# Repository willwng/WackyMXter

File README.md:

# WackyMXter
my custom keyboard.

## Features
- Wireless (bluetooth)
- Split (two halves can also be independent)
- Supports Choc and MX hotswap switches
- Ergonomic (for my hands at least)
- ZMK Support

## Project Format
- `gerber/`: Gerber files for the left and right side (includes BOM and placement files for assembly of shift register and diodes)
- `layout-editor/`: Layout of the keyboard for use at [keyboard layout editor](http://www.keyboard-layout-editor.com/)
- `pcb/`: KiCad files
- `zmk-firmware/`: Links to the ZMK firmware repo: [WackyMXter-zmk-firmware](https://github.com/willwng/WackyMXter-zmk-config)

## Materials
| **Item**              | **Quantity Required (per set)** |
|-----------------------|---------------------------------|
| PCBs                  |                               2 |
| [Xiao BLE](https://www.seeedstudio.com/Seeed-XIAO-BLE-nRF52840-p-5201.html)              |                               2 |
| Rotary Encoder        |                               2 |
| Encoder Knob          |                               2 |
| Hotswap Sockets       |                              68 |
| Choc Switches         |                              68 |
| Power Switch          |                               2 |
| JST Battery Connector |                               2 |
| LiPo Battery          |                               2 |
| Keycaps               |                              68 |

The power switch, JST connector, and LiPo battery are optional if you want the board to be wired (but this requires powering both halves)

## Notes
- Unless you update the footprint, be sure to get EC11(E) rotary encoder <- "E" being the key. I got an EC11(R) encoder and the legs didn't fit, causing me to clip them.
- I messed up the placement of the JST connector - it stands higher than the hotswap sockets, so for a caseless build it is unfortunately too tall to be on the bottom. I ended up mounting it on the front, but backward (to not interfere with the power switch), so this required reversing the polarity of the batteries

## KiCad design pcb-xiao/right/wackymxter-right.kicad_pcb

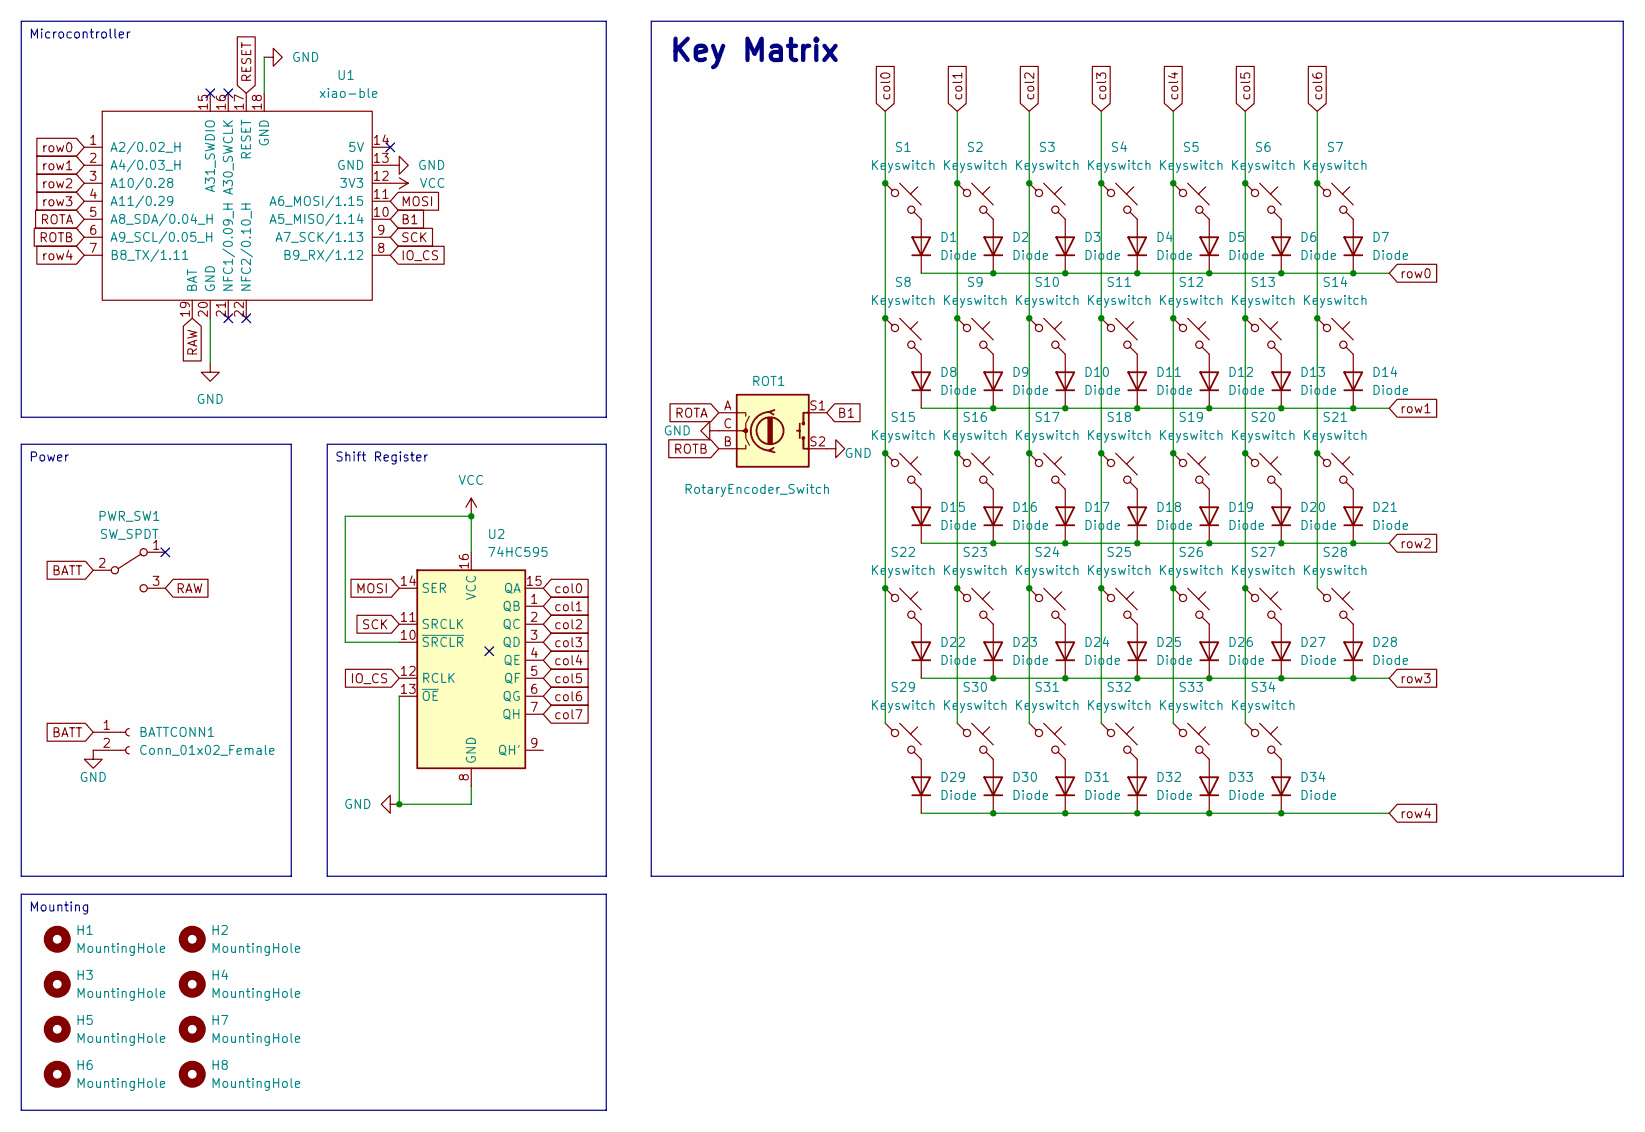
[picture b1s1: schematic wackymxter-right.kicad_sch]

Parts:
BATTCONN1: Conn_01x02_Female; JST_PH_S2B-PH-K_1x02_P2.00mm_Horizontal
D1, D2, D3, D4, D5, D6, D7, D8, D9, D10, D11, D12, D13, D14, D15, D16, D17, D18, D19, D20, D21, D22, D23, D24, D25, D26, D27, D28, D29, D30, D31, D32, D33, D34: Diode; HybridDiode
H1, H2, H3, H4, H5, H6, H7, H8: MountingHole; MountingHole_2.2mm_M2
PWR_SW1: SW_SPDT; SW_SPDT_CK_JS102011SAQN
ROT1: RotaryEncoder_Switch; RotaryEncoder_Alps_EC11E-Switch_Vertical_H20mm
S1, S2, S3, S4, S5, S6, S7, S8, S9, S10, S11, S12, S13, S14, S15, S16, S17, S18, S19, S20, S21, S22, S23, S24, S25, S26, S27, S28, S29, S30, S31, S32, S33, S34: Keyswitch; MX_Choc_Hotswap
U1: xiao-ble; xiao-ble-smd-cutout
U2: 74HC595; SOP-16_3.9x9.9mm_P1.27mm

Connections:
B1: ROT1.S1, U1.10 (A5_MISO/1.14)
BATT: BATTCONN1.1, PWR_SW1.2 (B)
GND: BATTCONN1.2, ROT1.C, ROT1.S2, U1.13 (GND), U1.18 (GND), U1.20 (GND), U2.8 (GND), U2.13 (~OE)
IO_CS: U1.8 (B9_RX/1.12), U2.12 (RCLK)
MOSI: U1.11 (A6_MOSI/1.15), U2.14 (SER)
unnamed: D1.2 (A), S1.2
unnamed: D2.2 (A), S2.2
unnamed: D3.2 (A), S3.2
unnamed: D4.2 (A), S4.2
unnamed: D5.2 (A), S5.2
unnamed: D6.2 (A), S6.2
unnamed: D7.2 (A), S7.2
unnamed: D8.2 (A), S8.2
unnamed: D9.2 (A), S9.2
unnamed: D10.2 (A), S10.2
unnamed: D11.2 (A), S11.2
unnamed: D12.2 (A), S12.2
unnamed: D13.2 (A), S13.2
unnamed: D14.2 (A), S14.2
unnamed: D15.2 (A), S15.2
unnamed: D16.2 (A), S16.2
unnamed: D17.2 (A), S17.2
unnamed: D18.2 (A), S18.2
unnamed: D19.2 (A), S19.2
unnamed: D20.2 (A), S20.2
unnamed: D21.2 (A), S21.2
unnamed: D22.2 (A), S22.2
unnamed: D23.2 (A), S23.2
unnamed: D24.2 (A), S24.2
unnamed: D25.2 (A), S25.2
unnamed: D26.2 (A), S26.2
unnamed: D27.2 (A), S27.2
unnamed: D28.2 (A), S28.2
unnamed: D29.2 (A), S29.2
unnamed: D30.2 (A), S30.2
unnamed: D31.2 (A), S31.2
unnamed: D32.2 (A), S32.2
unnamed: D33.2 (A), S33.2
unnamed: D34.2 (A), S34.2
RAW: PWR_SW1.3 (C), U1.19 (BAT)
RESET: U1.17 (RESET)
ROTA: ROT1.A, U1.5 (A8_SDA/0.04_H)
ROTB: ROT1.B, U1.6 (A9_SCL/0.05_H)
SCK: U1.9 (A7_SCK/1.13), U2.11 (SRCLK)
VCC: U1.12 (3V3), U2.10 (~SRCLR), U2.16 (VCC)
col0: S1.1, S8.1, S15.1, S22.1, S29.1, U2.15 (QA)
col1: S2.1, S9.1, S16.1, S23.1, S30.1, U2.1 (QB)
col2: S3.1, S10.1, S17.1, S24.1, S31.1, U2.2 (QC)
col3: S4.1, S11.1, S18.1, S25.1, S32.1, U2.3 (QD)
col4: S5.1, S12.1, S19.1, S26.1, S33.1, U2.4 (QE)
col5: S6.1, S13.1, S20.1, S27.1, S34.1, U2.5 (QF)
col6: S7.1, S14.1, S21.1, S28.1, U2.6 (QG)
col7: U2.7 (QH)
row0: D1.1 (K), D2.1 (K), D3.1 (K), D4.1 (K), D5.1 (K), D6.1 (K), D7.1 (K), U1.1 (A2/0.02_H)
row1: D8.1 (K), D9.1 (K), D10.1 (K), D11.1 (K), D12.1 (K), D13.1 (K), D14.1 (K), U1.2 (A4/0.03_H)
row2: D15.1 (K), D16.1 (K), D17.1 (K), D18.1 (K), D19.1 (K), D20.1 (K), D21.1 (K), U1.3 (A10/0.28)
row3: D22.1 (K), D23.1 (K), D24.1 (K), D25.1 (K), D26.1 (K), D27.1 (K), D28.1 (K), U1.4 (A11/0.29)
row4: D29.1 (K), D30.1 (K), D31.1 (K), D32.1 (K), D33.1 (K), D34.1 (K), U1.7 (B8_TX/1.11)

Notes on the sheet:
Microcontroller
Power
Shift Register
Key Matrix
Mounting

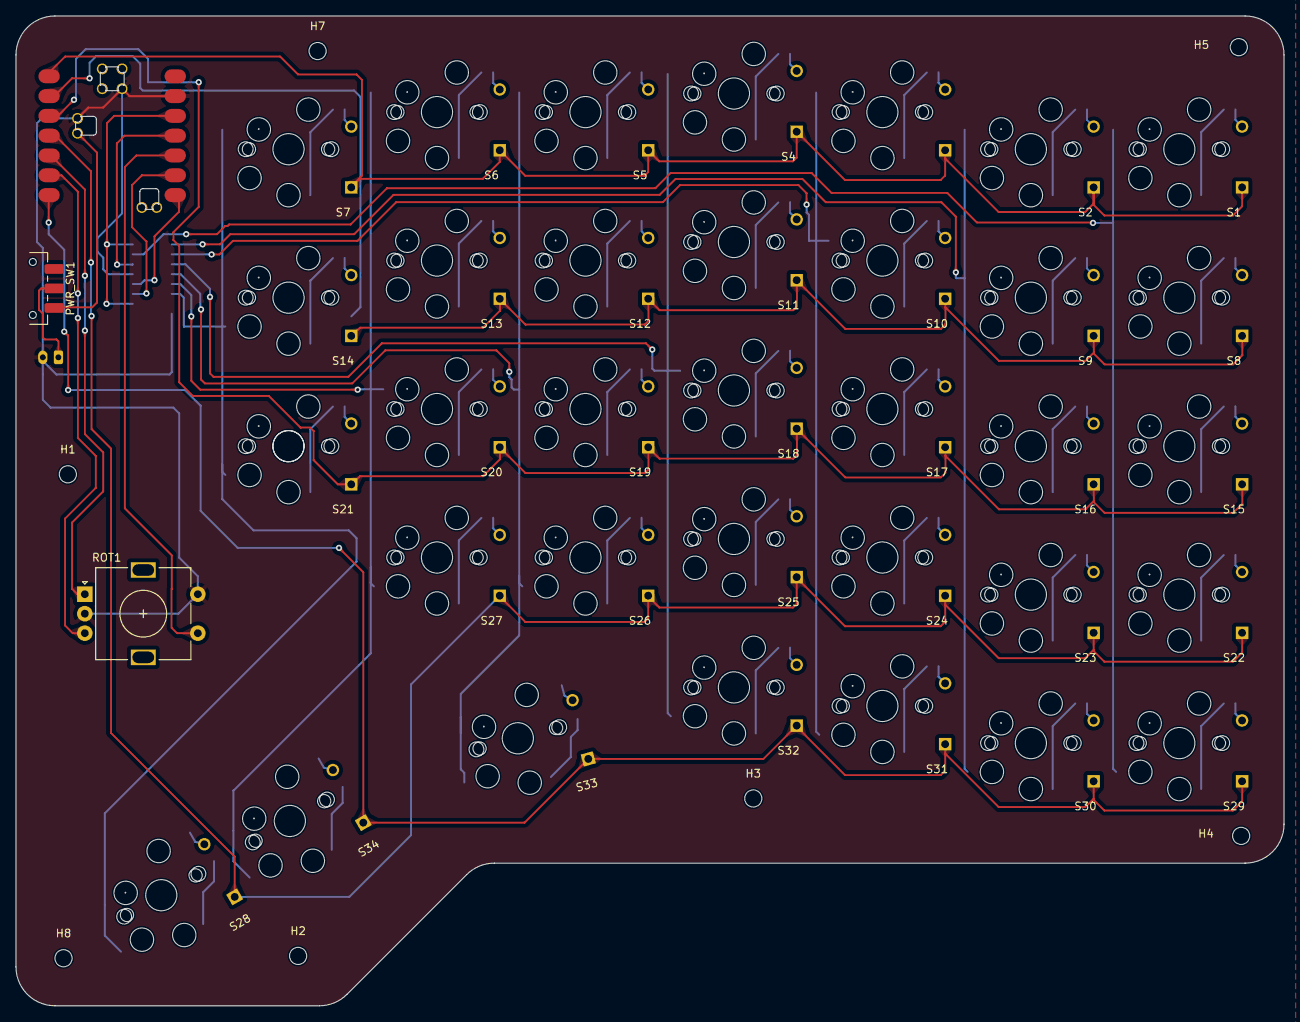
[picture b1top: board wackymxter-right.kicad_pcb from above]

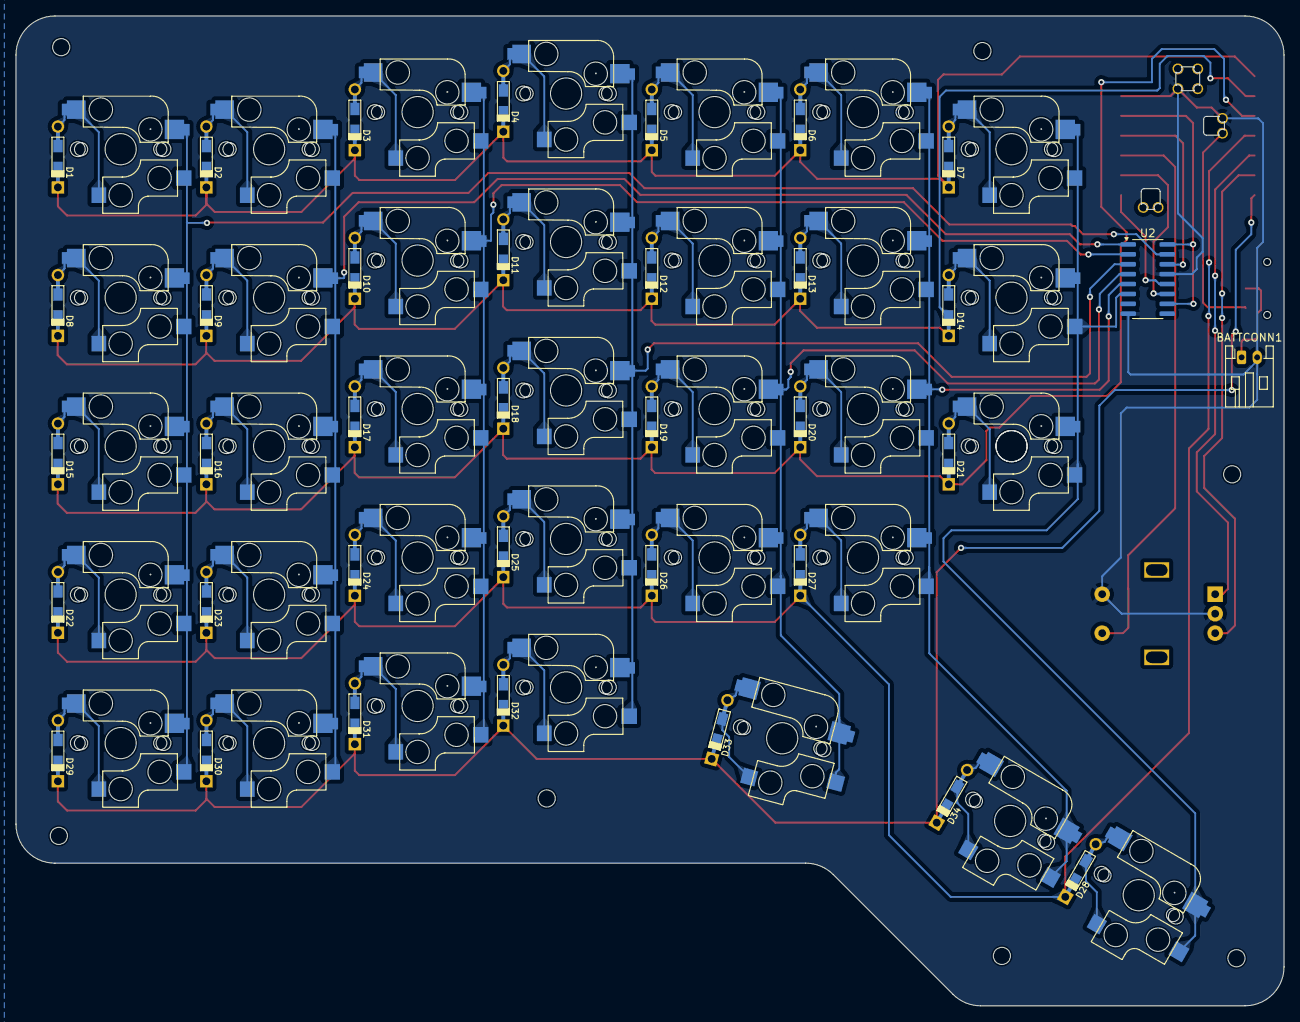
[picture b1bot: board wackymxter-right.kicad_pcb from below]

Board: 2 copper layers, 162.7 x 127.0 mm, 80 parts (2 on the bottom side), 56 nets.

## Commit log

2023-12-23 [KiCAD] start 35 key layout
2023-12-23 [KiCAD] switch to RP2040
2023-12-24 [KiCAD] V0.1: fully connected pcb
2023-12-24 [KiCAD] Pi Pico W with LEDs and Rotary Encoder
2023-12-26 [KiCAD] rev 0.3: dual diodes, optional hotswap
2024-01-02 [KiCAD] draft of left and right with 1.5u and fully connected
2024-01-04 [KiCAD] better copper fills
2024-01-07 [Layout Editor] Update full and right layout
2024-06-26 Progress
2024-07-31 Insane progresgress
2024-08-05 Cooler cutout out and match schematics
2024-08-23 production!
2024-08-23 submodules
2024-08-23 reorganize
2024-08-23 rename
2024-08-23 firmware submodule
2024-08-28 Update submodule
